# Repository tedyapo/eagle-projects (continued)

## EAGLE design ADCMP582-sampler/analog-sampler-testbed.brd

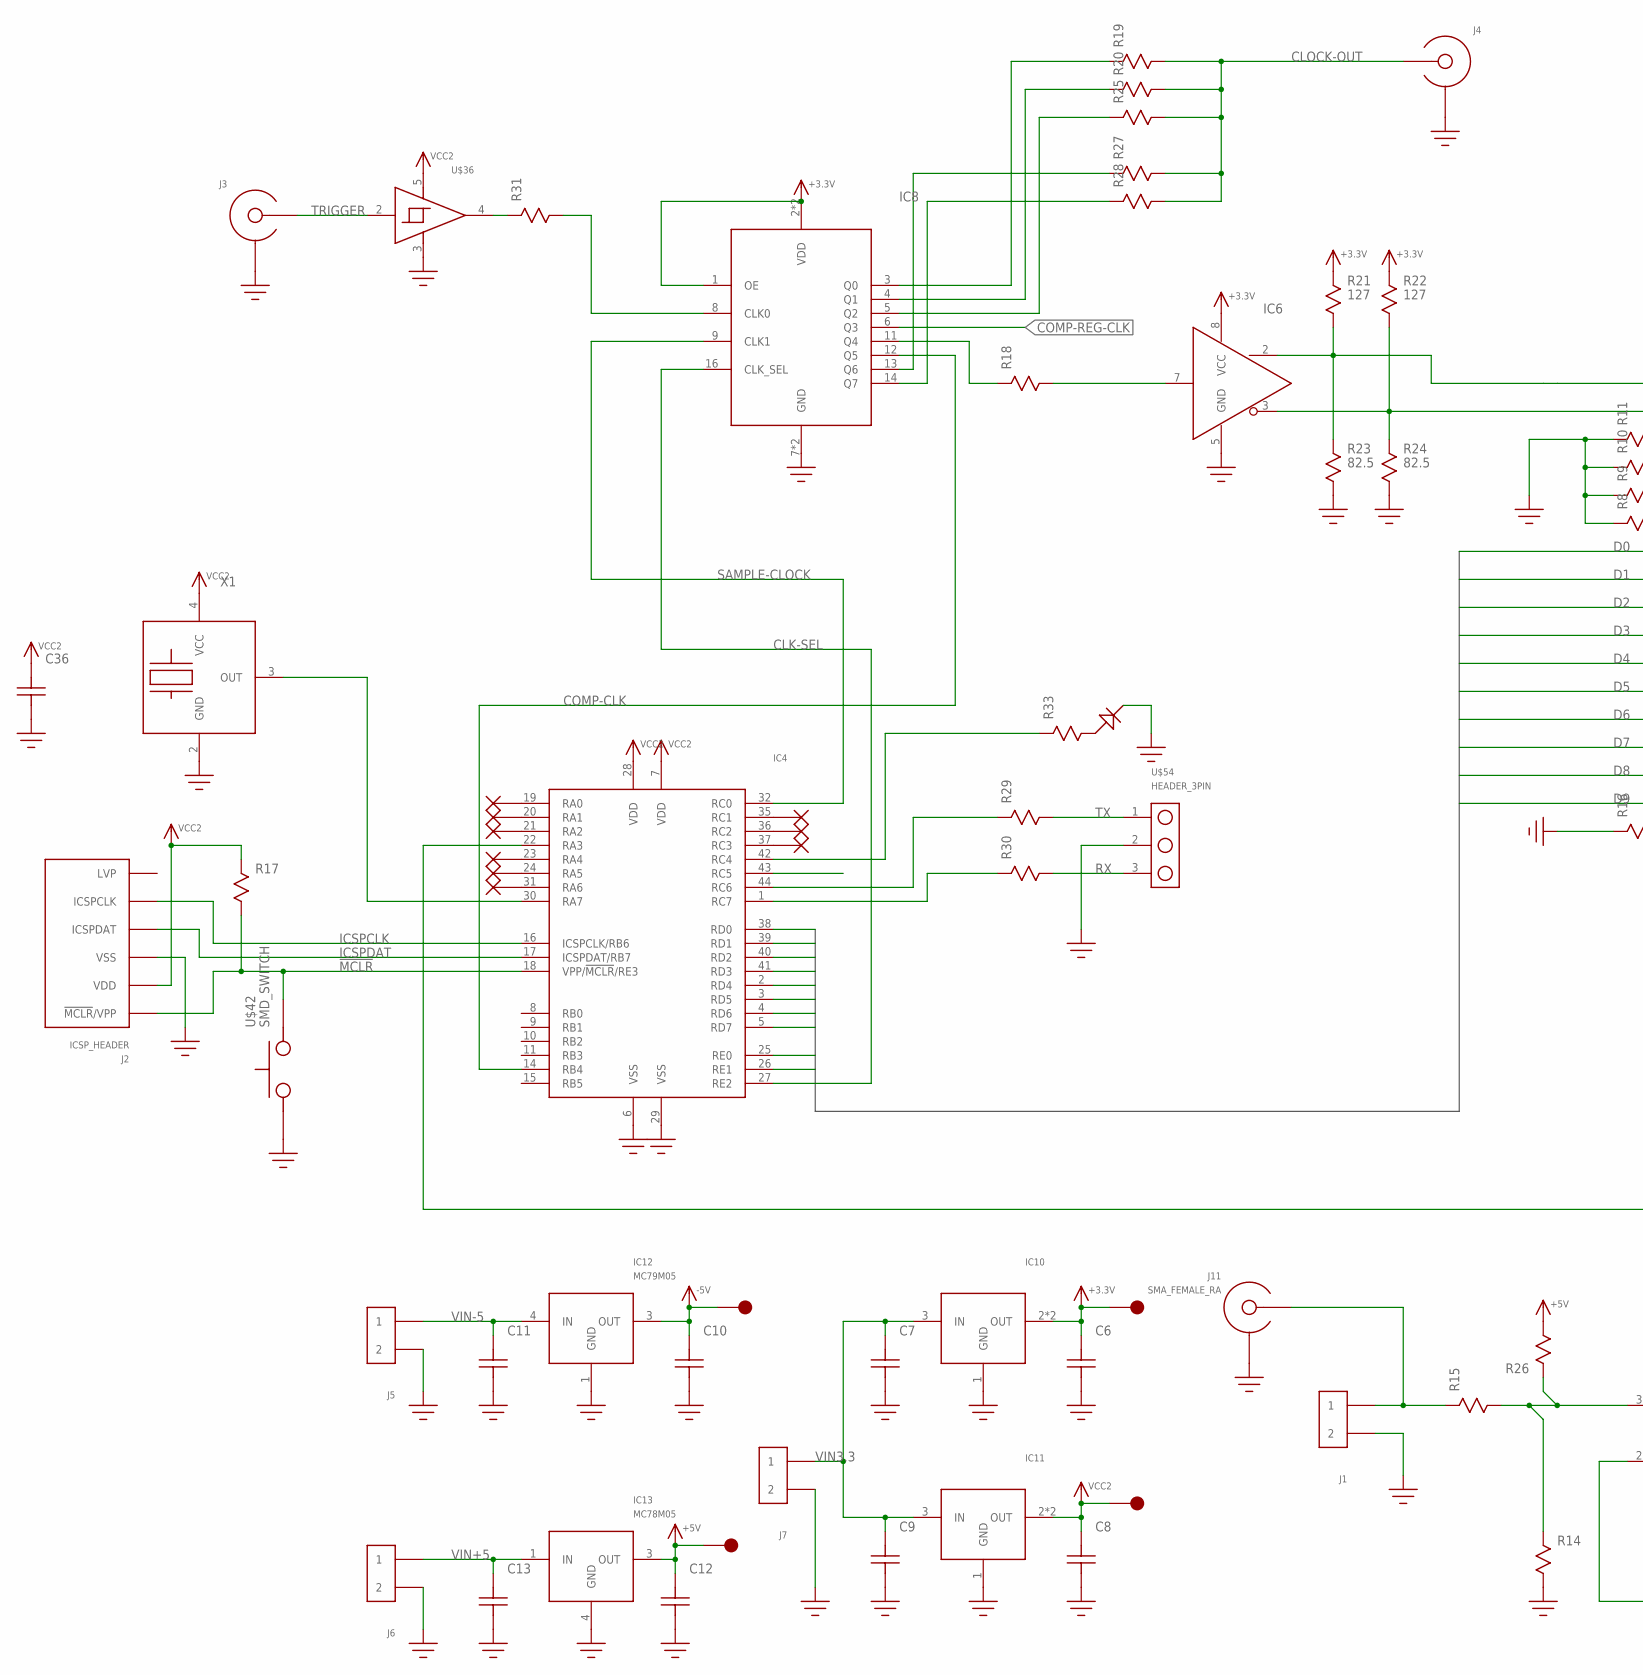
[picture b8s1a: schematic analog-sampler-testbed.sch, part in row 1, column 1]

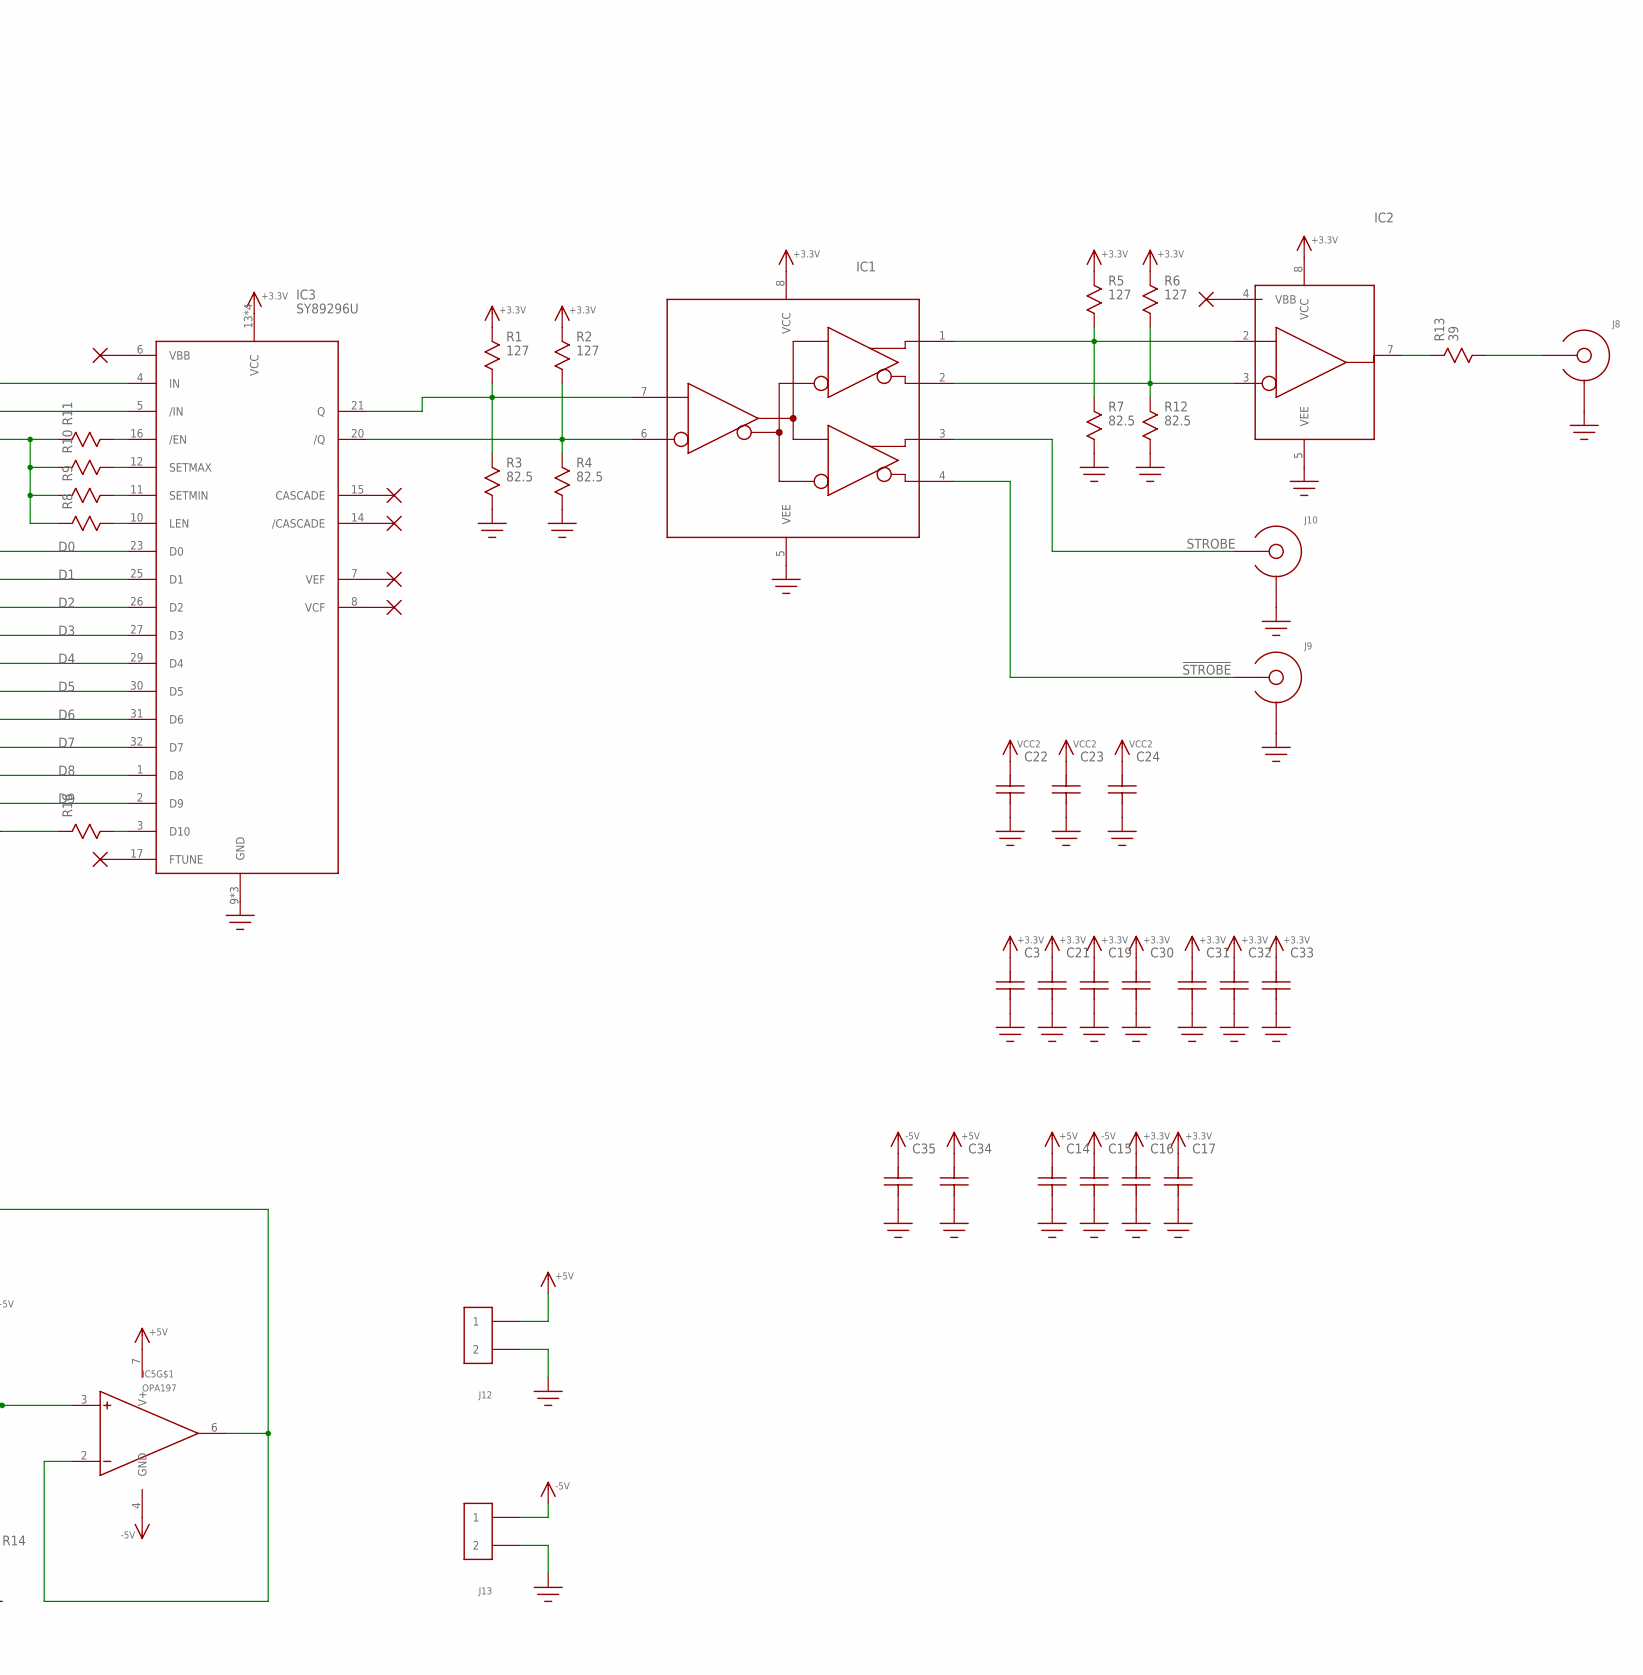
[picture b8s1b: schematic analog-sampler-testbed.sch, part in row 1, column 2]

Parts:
C3, C14, C15, C16, C17, C19, C21, C22, C23, C24, C30, C31, C32, C33, C34, C35, C36: C0603
C6, C7, C8, C9, C10, C11, C12, C13: C1206; 1206
IC1: SY10EP11U; SOIC8
IC2: MC100EPT21; SOIC8
IC3: SY89296U; TQFP32_7X7
IC4: PIC16F15376; TQFP44
IC5: OPA197; SOIC8
IC6: MC100LVELT20; SOIC8
IC8: SI53360TSSOP16; TSSOP16
IC10, IC11: AZ1117E; SOT-223
IC12: MC79M05; DPAK
IC13: MC78M05; DPAK
J1, J12, J13: HEADER_2PIN
J2: ICSP_HEADER; HEADER_6PIN
J3, J4, J8, J9, J10: SMA-EDGE-LAUNCH4L-4020-TAPER-FIXED; SMA_EDGE_LAUNCH_4L_4020_TAPER_FIXED
J5, J6, J7: HEADER_2PINSCREW-TERM; FCI_20020316_SCREW_TERM_2P
J11: SMA_FEMALE_RA; SMA_RA_PCB
P3, P4, P5, P6: ICSP_PAD
R1, R2, R5, R6, R21, R22: 127; R0603
R3, R4, R7, R12, R23, R24: 82.5; R0603
R8, R9, R10, R11, R19, R20, R25, R27, R28: R0402; 0402
R13: 39; R0603
R14, R15, R16, R17, R18, R26, R29, R30, R31, R33: R0603
U$36: 74LVC1G17; SOT23-5
U$42: SMD_SWITCH
U$54: HEADER_3PIN
U$88: LED_0603
X1: XTAL_OSC; XTAL_3.2X5

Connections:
!MCLR!: IC4.18 (VPP/!MCLR!/RE3), J2.1 (!MCLR!/VPP), R17.P$2, U$42.P$3, U$42.P$4
!STROBE!: IC1.4 (!Q1!), J9.CENTER@1 (CENTER), J9.P$3 (CENTER)
+3.3V: C3.P$2, C6.P$2, C16.P$2, C17.P$2, C19.P$2, C21.P$2, C30.P$2, C31.P$2, C32.P$2, C33.P$2, IC1.8 (VCC), IC2.8 (VCC), IC3.13 (VCC), IC3.18 (VCC), IC3.19 (VCC), IC3.22 (VCC), IC6.8 (VCC), IC8.1 (OE), IC8.2 (VDD), IC8.15 (VDD), IC10.2 (OUT), IC10.4 (OUT), P5.P$1, R1.P$1, R2.P$1, R5.P$1, R6.P$1, R21.P$1, R22.P$1
+5V: C12.P$2, C14.P$2, C34.P$2, IC5.7 (V+), IC13.3 (OUT), J12.1, P4.P$1, R26.P$2
-5V: C10.P$2, C15.P$2, C35.P$2, IC5.4 (GND), IC12.3 (OUT), J13.1, P3.P$1
CLK-SEL: IC4.27 (RE2), IC8.16 (CLK_SEL)
CLOCK-OUT: J4.CENTER@1 (CENTER), J4.P$3 (CENTER), R19.2, R20.2, R25.2, R27.2, R28.2
COMP-CLK: IC4.14 (RB4), IC8.12 (Q5)
COMP-REG-CLK: IC8.6 (Q3)
D0: IC3.23 (D0), IC4.38 (RD0)
D1: IC3.25 (D1), IC4.39 (RD1)
D2: IC3.26 (D2), IC4.40 (RD2)
D3: IC3.27 (D3), IC4.41 (RD3)
D4: IC3.29 (D4), IC4.2 (RD4)
D5: IC3.30 (D5), IC4.3 (RD5)
D6: IC3.31 (D6), IC4.4 (RD6)
D7: IC3.32 (D7), IC4.5 (RD7)
D8: IC3.1 (D8), IC4.25 (RE0)
D9: IC3.2 (D9), IC4.26 (RE1)
GND: C3.P$1, C6.P$1, C7.P$1, C8.P$1, C9.P$1, C10.P$1, C11.P$1, C12.P$1, C13.P$1, C14.P$1, C15.P$1, C16.P$1, C17.P$1, C19.P$1, C21.P$1, C22.P$1, C23.P$1, C24.P$1, C30.P$1, C31.P$1, C32.P$1, C33.P$1, C34.P$1, C35.P$1, C36.P$1, IC1.5 (VEE), IC2.5 (VEE), IC3.9 (GND), IC3.24 (GND), IC3.28 (GND), IC4.6 (VSS), IC4.29 (VSS), IC6.5 (GND), IC8.7 (GND), IC8.10 (GND), IC10.1 (GND), IC11.1 (GND), IC12.1 (GND), IC13.4 (GND), J1.2, J2.3 (VSS), J3.BOTTOM_GND (SHIELD), J3.GND@1 (SHIELD), J3.GND@2 (SHIELD), J3.GND@3 (SHIELD), J3.GND@4 (SHIELD), J3.GND@5 (SHIELD), J3.GND@6 (SHIELD), J3.GND@7 (SHIELD), J3.GND@8 (SHIELD), J3.GND@14 (SHIELD), J3.GND@15 (SHIELD), J3.GND@16 (SHIELD), J3.GND@17 (SHIELD), J3.GND_PAD1 (SHIELD), J3.GND_PAD2 (SHIELD), J3.P$1 (SHIELD), J3.P$2 (SHIELD), J4.BOTTOM_GND (SHIELD), J4.GND@1 (SHIELD), J4.GND@2 (SHIELD), J4.GND@3 (SHIELD), J4.GND@4 (SHIELD), J4.GND@5 (SHIELD), J4.GND@6 (SHIELD), J4.GND@7 (SHIELD), J4.GND@8 (SHIELD), J4.GND@14 (SHIELD), J4.GND@15 (SHIELD), J4.GND@16 (SHIELD), J4.GND@17 (SHIELD), J4.GND_PAD1 (SHIELD), J4.GND_PAD2 (SHIELD), J4.P$1 (SHIELD), J4.P$2 (SHIELD), J5.P$2 (2), J6.P$2 (2), J7.P$2 (2), J8.BOTTOM_GND (SHIELD), J8.GND@1 (SHIELD), J8.GND@2 (SHIELD), J8.GND@3 (SHIELD), J8.GND@4 (SHIELD), J8.GND@5 (SHIELD), J8.GND@6 (SHIELD), J8.GND@7 (SHIELD), J8.GND@8 (SHIELD), J8.GND@14 (SHIELD), J8.GND@15 (SHIELD), J8.GND@16 (SHIELD), J8.GND@17 (SHIELD), J8.GND_PAD1 (SHIELD), J8.GND_PAD2 (SHIELD), J8.P$1 (SHIELD), J8.P$2 (SHIELD), J9.BOTTOM_GND (SHIELD), J9.GND@1 (SHIELD), J9.GND@2 (SHIELD), J9.GND@3 (SHIELD), J9.GND@4 (SHIELD), J9.GND@5 (SHIELD), J9.GND@6 (SHIELD), J9.GND@7 (SHIELD), J9.GND@8 (SHIELD), J9.GND@14 (SHIELD), J9.GND@15 (SHIELD), J9.GND@16 (SHIELD), J9.GND@17 (SHIELD), J9.GND_PAD1 (SHIELD), J9.GND_PAD2 (SHIELD), J9.P$1 (SHIELD), J9.P$2 (SHIELD), J10.BOTTOM_GND (SHIELD), J10.GND@1 (SHIELD), J10.GND@2 (SHIELD), J10.GND@3 (SHIELD), J10.GND@4 (SHIELD), J10.GND@5 (SHIELD), J10.GND@6 (SHIELD), J10.GND@7 (SHIELD), J10.GND@8 (SHIELD), J10.GND@14 (SHIELD), J10.GND@15 (SHIELD), J10.GND@16 (SHIELD), J10.GND@17 (SHIELD), J10.GND_PAD1 (SHIELD), J10.GND_PAD2 (SHIELD), J10.P$1 (SHIELD), J10.P$2 (SHIELD), J11.SHIELD@1 (SHIELD), J11.SHIELD@2 (SHIELD), J11.SHIELD@3 (SHIELD), J11.SHIELD@4 (SHIELD), J12.2, J13.2, R3.P$2, R4.P$2, R7.P$2, R8.1, R9.1, R10.1, R11.1, R12.P$2, R14.P$2, R16.P$1, R23.P$2, R24.P$2, U$36.3 (GND), U$42.P$1, U$42.P$2, U$54.2, U$88.C, X1.2 (GND)
ICSPCLK: IC4.16 (ICSPCLK/RB6), J2.5 (ICSPCLK)
ICSPDAT: IC4.17 (ICSPDAT/RB7), J2.4 (ICSPDAT)
LE_N: IC1.7 (D), IC3.21 (Q), R1.P$2, R3.P$1
LE_P1: IC1.6 (!D!), IC3.20 (/Q), R2.P$2, R4.P$1
unnamed: R31.P$1, U$36.4 (OUT)
unnamed: IC1.1 (Q0), IC2.2 (D), R5.P$2, R7.P$1
unnamed: IC1.2 (!Q0!), IC2.3 (!D!), R6.P$2, R12.P$1
unnamed: IC2.7 (Q), R13.P$1
unnamed: IC3.16 (/EN), R11.2
unnamed: IC3.12 (SETMAX), R10.2
unnamed: IC3.11 (SETMIN), R9.2
unnamed: IC3.10 (LEN), R8.2
unnamed: J8.CENTER@1 (CENTER), J8.P$3 (CENTER), R13.P$2
unnamed: IC3.4 (IN), IC6.2 (Q), R21.P$2, R23.P$1
unnamed: IC4.22 (RA3), IC5.2 (-), IC5.6 (OUT)
unnamed: IC8.11 (Q4), R18.P$1
unnamed: IC5.3 (+), R14.P$1, R15.P$2, R26.P$1
unnamed: J1.1, J11.CENTER, R15.P$1
unnamed: IC3.5 (/IN), IC6.3 (!Q!), R22.P$2, R24.P$1
unnamed: IC8.8 (CLK0), R31.P$2
unnamed: IC4.30 (RA7), X1.3 (OUT)
unnamed: IC4.42 (RC4), R33.P$1
unnamed: R33.P$2, U$88.A
unnamed: IC3.3 (D10), R16.P$2
unnamed: IC6.7 (D), R18.P$2
unnamed: IC8.14 (Q7), R28.1
unnamed: IC8.13 (Q6), R27.1
unnamed: IC8.5 (Q2), R25.1
unnamed: IC8.4 (Q1), R20.1
unnamed: IC8.3 (Q0), R19.1
unnamed: IC4.44 (RC6), R29.P$1
unnamed: IC4.1 (RC7), R30.P$1
RX: R30.P$2, U$54.3
SAMPLE-CLOCK: IC4.32 (RC0), IC8.9 (CLK1)
STROBE: IC1.3 (Q1), J10.CENTER@1 (CENTER), J10.P$3 (CENTER)
TRIGGER: J3.CENTER@1 (CENTER), J3.P$3 (CENTER), U$36.2 (IN)
TX: R29.P$2, U$54.1
VCC2: C8.P$2, C22.P$2, C23.P$2, C24.P$2, C36.P$2, IC4.7 (VDD), IC4.28 (VDD), IC11.2 (OUT), IC11.4 (OUT), J2.2 (VDD), P6.P$1, R17.P$1, U$36.5 (VCC), X1.4 (VCC)
VIN3.3: C7.P$2, C9.P$2, IC10.3 (IN), IC11.3 (IN), J7.P$1 (1)
VIN+5: C13.P$2, IC13.1 (IN), J6.P$1 (1)
VIN-5: C11.P$2, IC12.4 (IN), J5.P$1 (1)

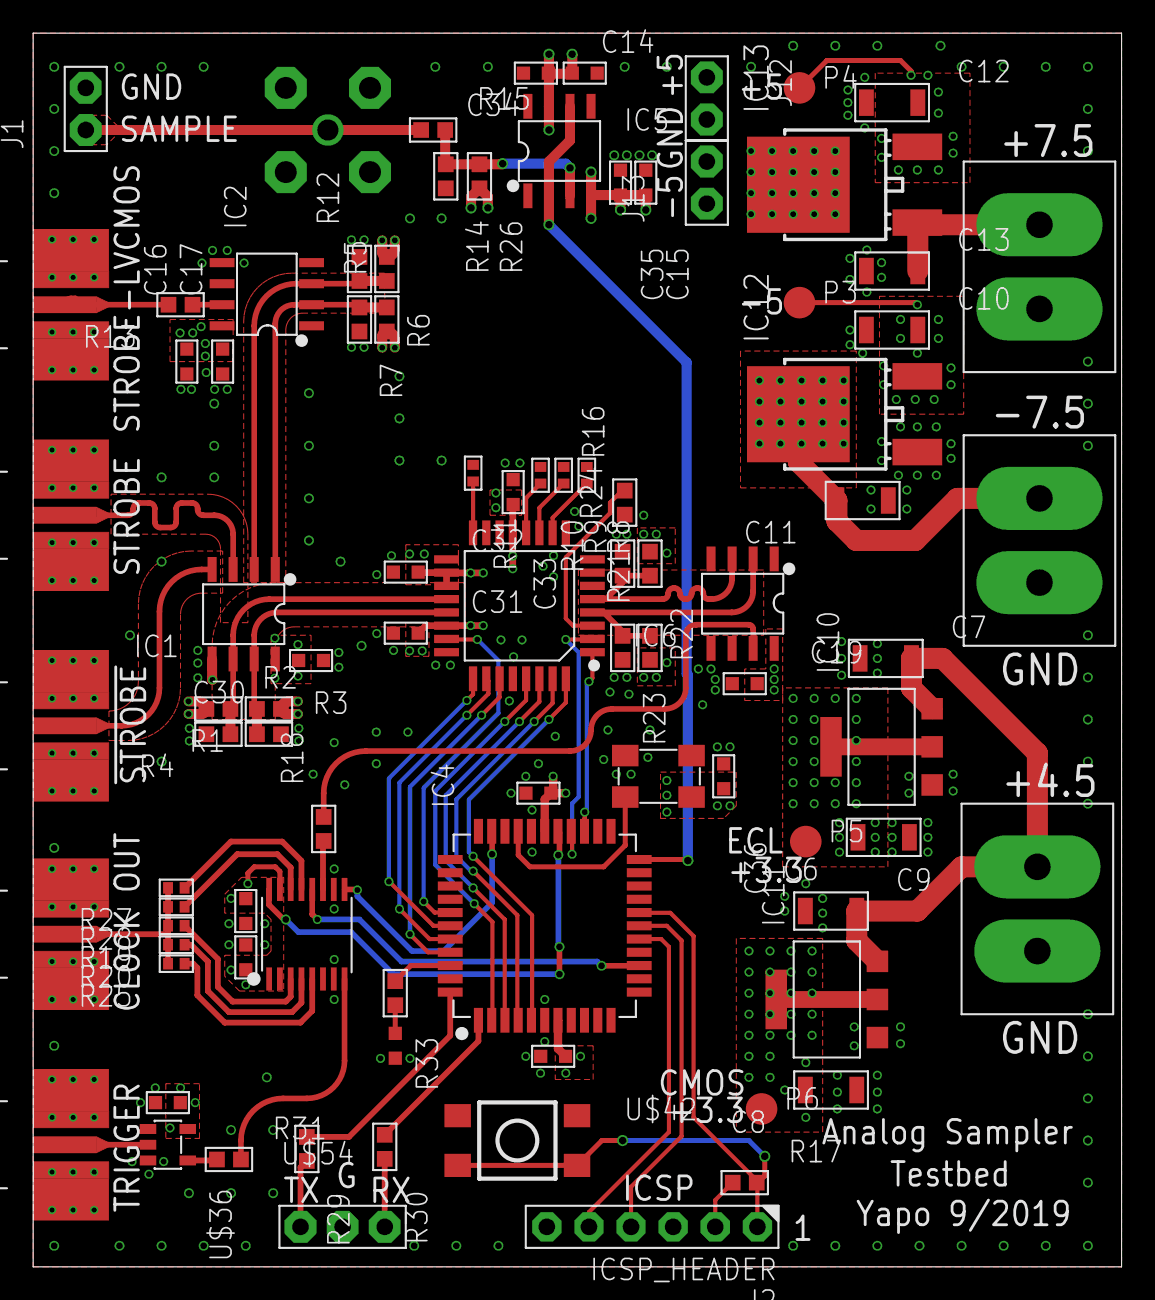
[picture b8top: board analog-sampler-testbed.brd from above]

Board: 4 copper layers, 65.7 x 74.4 mm, 90 parts (0 on the bottom side), 60 nets.

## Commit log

2019-06-08 checkpoint
2019-07-12 added sma footprint lib
2019-08-19 checkpoint/merge
